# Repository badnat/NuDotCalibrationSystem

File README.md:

# NuDotCalibrationSystem

This project is for the NuDot Experiment https://jgruszko.web.unc.edu/experiments/. I am a student at UNC who will be graduating in May 2022. I am working with Dr. Gruszko to develop the code and electronics to control the calibration system for the NuDot experiment. The goal of this experiment is to detect neutrinoless double beta decay. Neutrinoless double beta decay is a very rare phenomenon. Because of this, it is difficult to distinguish signal from background during detection. NuDots goal is to reduce the background by detecting cherenkov radiation from single electron events produced by background events as opposed to the double electrons given off by double beta decay. 
 
The goal of my code and electronics is to move a point beta ray source to an exact height, inclination, and rotation. Knowing these allows NuDot to calibrate the precise timings given by the detectors. These timings are extremely important for event building, where we determine details about the event causing the signal such as the position and energy. 

## My Approach and Method
Having previously taken a class full dedicated to working with microcontrollers, my first thought for this project was to use a Raspberry Pi. I ruled out Arduinos because I needed a file system to save multiple files and wanted the flexibility of a microcontroller with an OS for testing purposes. The problem ultimately boils down to moving 3 stepper motors into position, verifying the accuracy of that position, and recording that position for and future movements of the stepper. 
 
I achieved these objectives by using python code to control the stepper motors and a c++ program to read the data from the stepper encoders, interpret the data, and store the position in a file. The python code will only move the stepper and the c++ code will only determine its position. This allows me to independently verify the positions of the steppers and compensate for any step skipping that might occur. This ensures that we always accurately know the positions of the steppers which is important for both calibration and mechanical reasons. Obviously we need to accurately know the position of the beta source to calibrate the system, but there are also a few mechanical hard stops that the steppers would be unable to push past (blocked by a lot of metal). I could have used a sensor to determine the position in space but decided to make my code very robust to avoid the issue all together. 

#### Code Structure
I decided on an object oriented approach for ease of use and abstraction. The [Calibrator](https://github.com/badnat/NuDotCalibrationSystem/blob/main/calibrator.py) object is primarily for abstraction and handling error handling/edge cases. It holds all of the [Stepper](https://github.com/badnat/NuDotCalibrationSystem/blob/main/stepper.py) objects which send the signals to the stepper motors to move them. The [Stepper](https://github.com/badnat/NuDotCalibrationSystem/blob/main/stepper.py) objects also use bash commands to start up the [encoder](https://github.com/badnat/NuDotCalibrationSystem/blob/main/encoder.cpp) code for that stepper motor. 

## Assembled Calibration System

## Challenges and Future Improvements
- Fully implementation of code and handling a few more edge cases (almost finished)
- Implement code for the Daq system to control the Rpi remotely using ssh keys
- Finalize Electronics using a custom PCB and CAT6 cable to send signals to the steppers and to the Pi from the encoders

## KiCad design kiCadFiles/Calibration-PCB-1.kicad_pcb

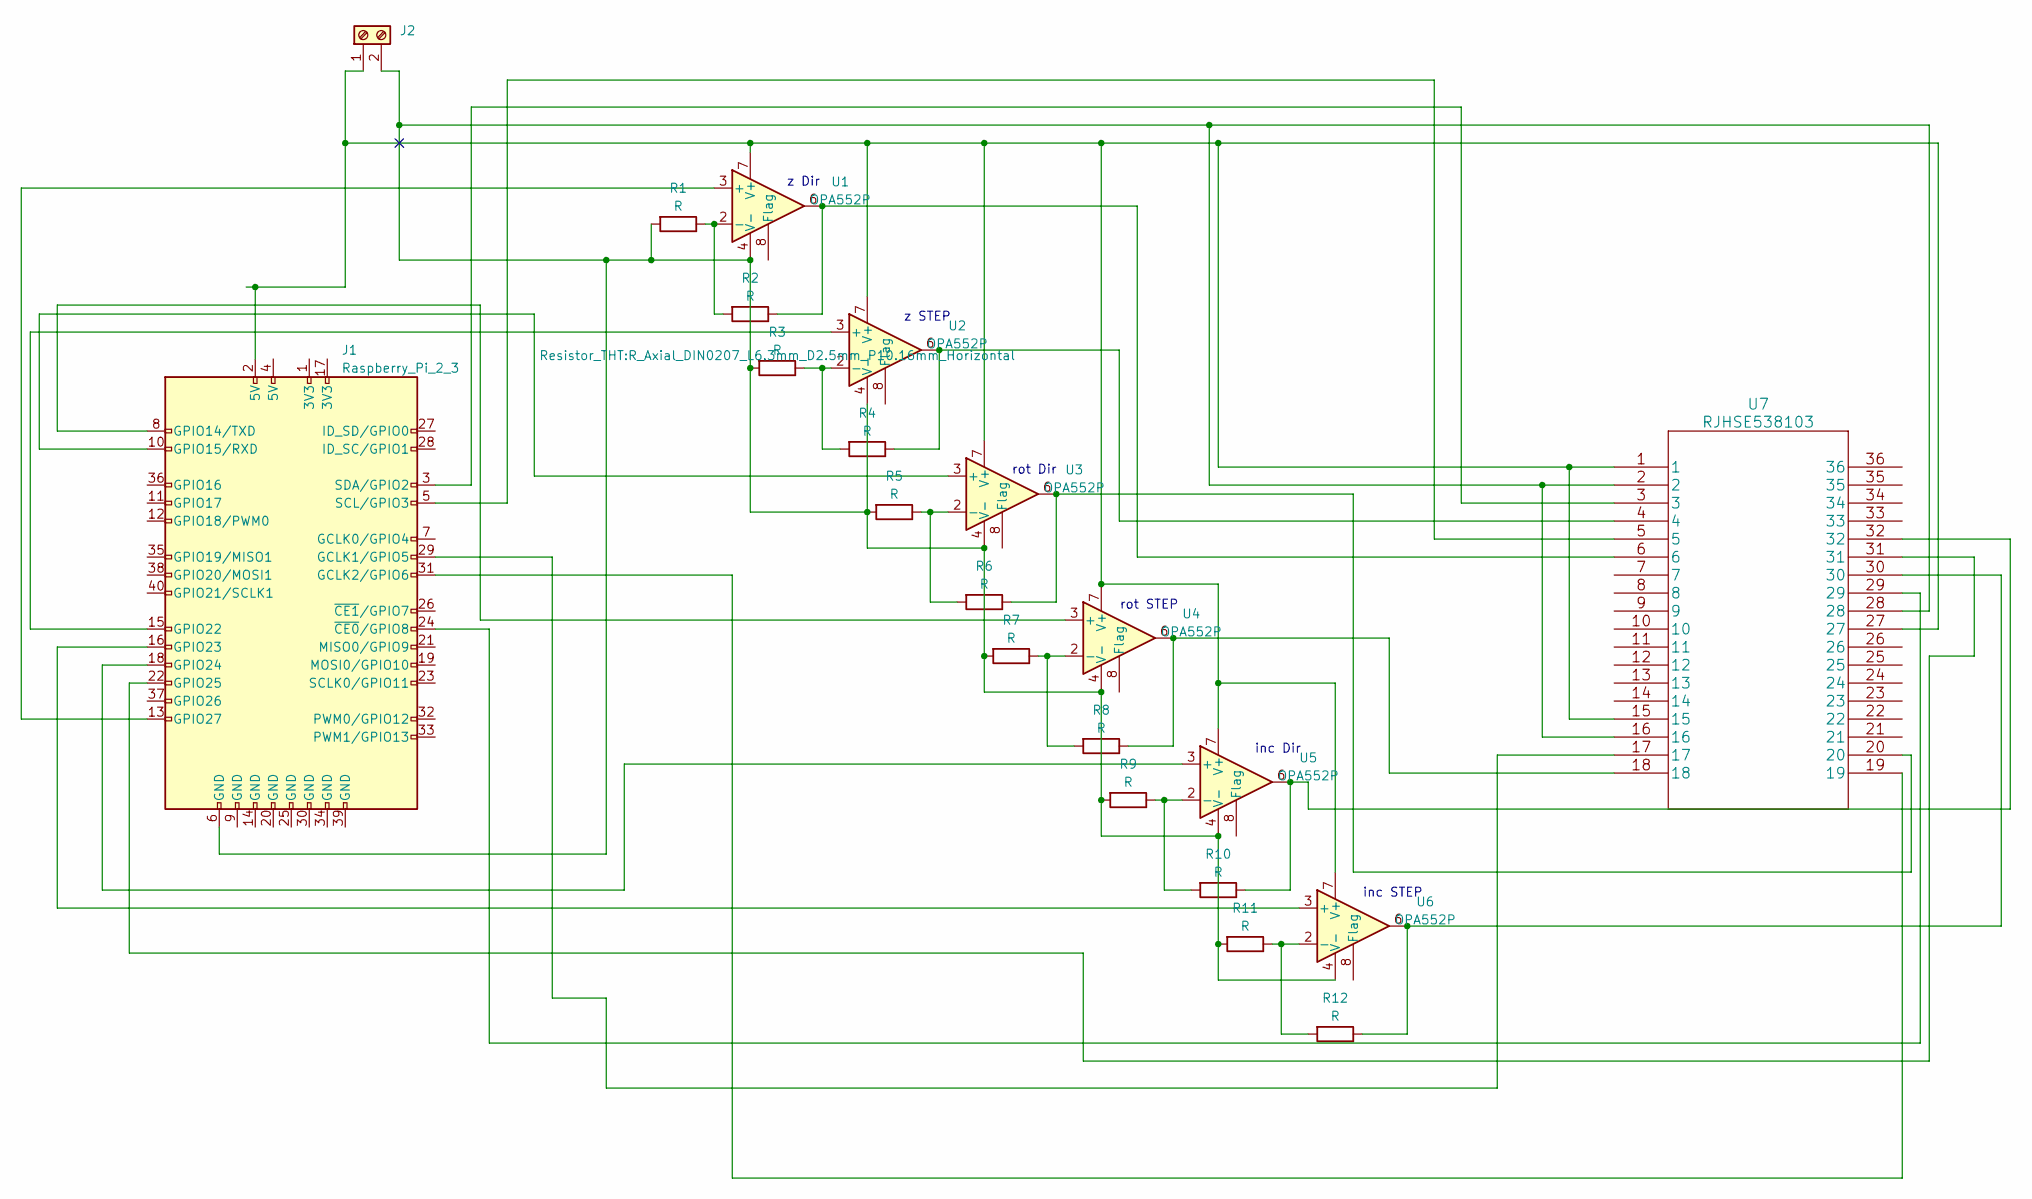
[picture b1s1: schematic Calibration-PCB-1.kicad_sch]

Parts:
J1: Raspberry_Pi_2_3; PinHeader_2x20_P2.54mm_Vertical
J2: (no value)
R1, R2, R3, R4, R5, R6, R7, R8, R9, R10, R11, R12: R; R_Axial_DIN0207_L6.3mm_D2.5mm_P10.16mm_Horizontal
U1, U2, U3, U4, U5, U6: OPA552P; DIP-8_W7.62mm
U7: RJHSE538103

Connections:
unnamed: J1.2 (5V), J2.1, U1.7 (V+), U2.7 (V+), U3.7 (V+), U4.7 (V+), U5.7 (V+), U6.7 (V+), U7.1, U7.15, U7.27
unnamed: J1.29 (GCLK1/GPIO5), U7.17
unnamed: J1.31 (GCLK2/GPIO6), U7.19
unnamed: J1.6 (GND), J2.2, R1.2, R3.2, R5.2, R7.2, R9.2, R11.2, U1.4 (V-), U2.4 (V-), U3.4 (V-), U4.4 (V-), U5.4 (V-), U6.4 (V-), U7.2, U7.16, U7.28
unnamed: J1.13 (GPIO27), U1.3 (+)
unnamed: J1.5 (SCL/GPIO3), U7.5
unnamed: J1.3 (SDA/GPIO2), U7.3
unnamed: R2.1, U1.6, U7.6
unnamed: R4.1, U2.6, U7.4
unnamed: R6.1, U3.6, U7.20
unnamed: R8.1, U4.6, U7.18
unnamed: R1.1, R2.2, U1.2 (-)
unnamed: J1.15 (GPIO22), U2.3 (+)
unnamed: R3.1, R4.2, U2.2 (-)
unnamed: J1.10 (GPIO15/RXD), U3.3 (+)
unnamed: R5.1, R6.2, U3.2 (-)
unnamed: J1.8 (GPIO14/TXD), U4.3 (+)
unnamed: R7.1, R8.2, U4.2 (-)
unnamed: J1.18 (GPIO24), U5.3 (+)
unnamed: R9.1, R10.2, U5.2 (-)
unnamed: J1.16 (GPIO23), U6.3 (+)
unnamed: R11.1, R12.2, U6.2 (-)
unnamed: J1.24 (~CE0/GPIO8), U7.29
unnamed: R12.1, U6.6, U7.30
unnamed: J1.22 (GPIO25), U7.31
unnamed: R10.1, U5.6, U7.32

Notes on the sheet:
rot STEP
rot Dir
z STEP
inc Dir
inc STEP
z Dir

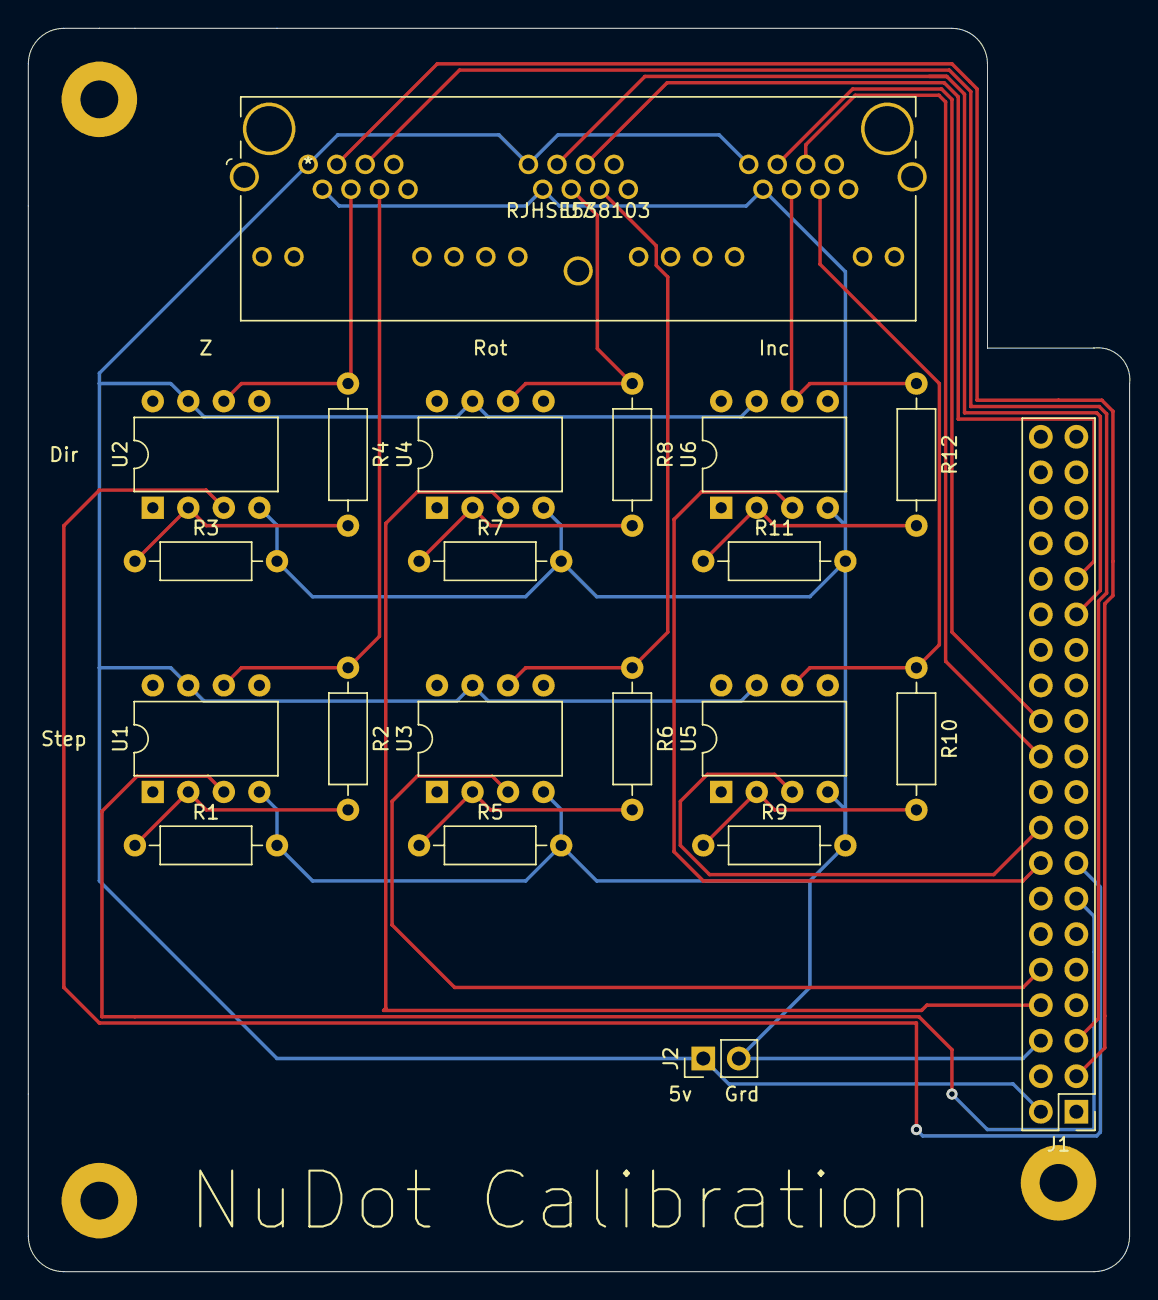
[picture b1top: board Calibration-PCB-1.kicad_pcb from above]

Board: 2 copper layers, 78.8 x 88.9 mm, 21 parts (0 on the bottom side), 26 nets.

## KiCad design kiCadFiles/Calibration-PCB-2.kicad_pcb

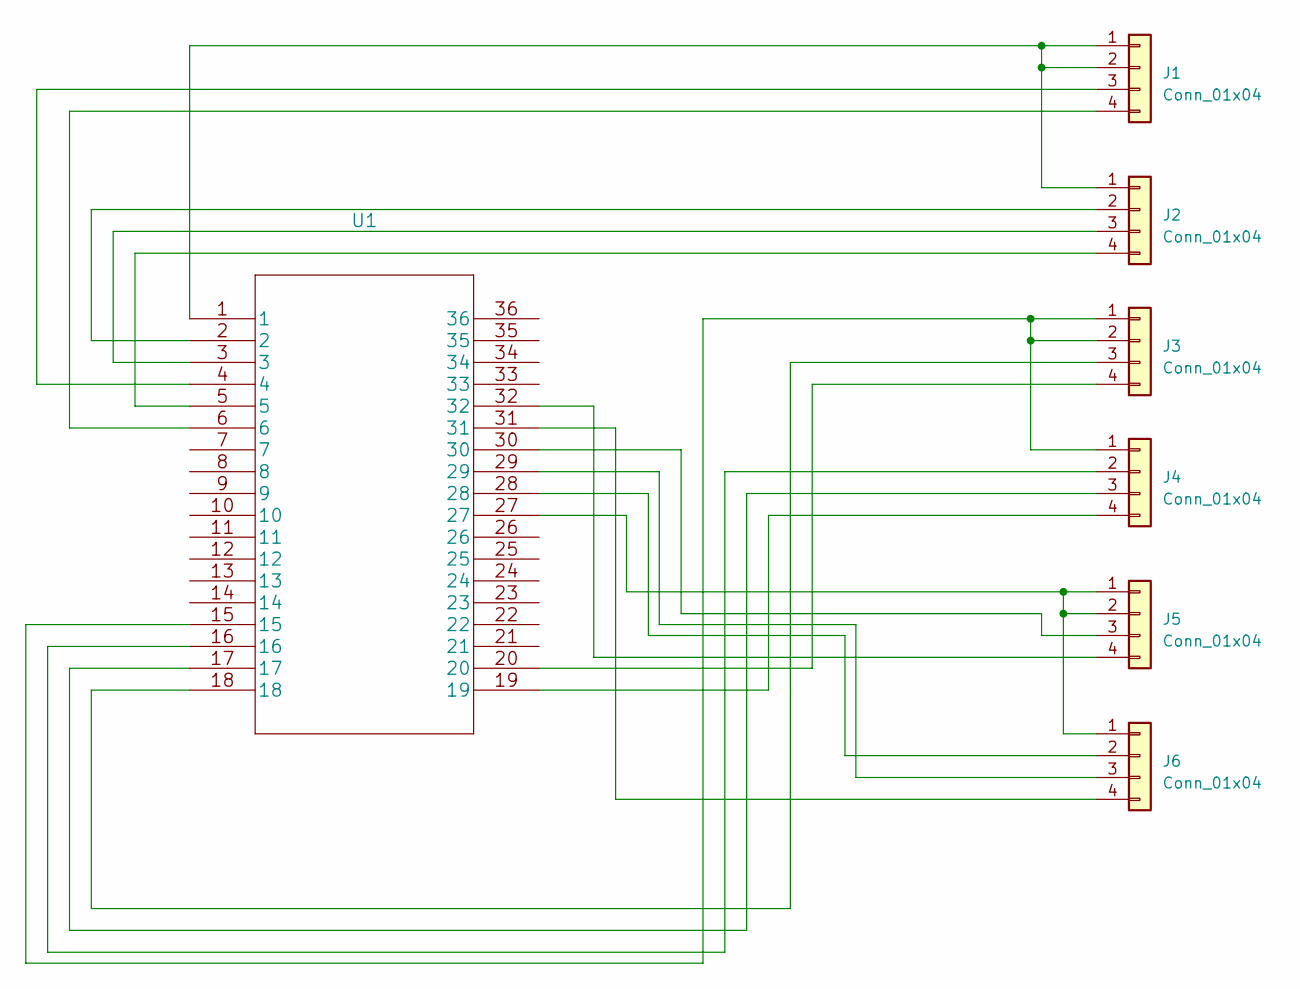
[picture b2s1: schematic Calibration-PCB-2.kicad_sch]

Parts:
J1, J2, J3, J4, J5, J6: Conn_01x04; PinSocket_1x04_P2.54mm_Vertical
U1: (no value)

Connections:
unnamed: J1.1, J1.2, J2.1, U1.1
unnamed: J1.3, U1.4
unnamed: J1.4, U1.6
unnamed: J2.2, U1.2
unnamed: J2.3, U1.3
unnamed: J2.4, U1.5
unnamed: J3.1, J3.2, J4.1, U1.15
unnamed: J3.3, U1.18
unnamed: J3.4, U1.20
unnamed: J4.2, U1.16
unnamed: J4.3, U1.17
unnamed: J4.4, U1.19
unnamed: J5.1, J5.2, J6.1, U1.27
unnamed: J5.3, U1.30
unnamed: J5.4, U1.32
unnamed: J6.2, U1.28
unnamed: J6.3, U1.29
unnamed: J6.4, U1.31

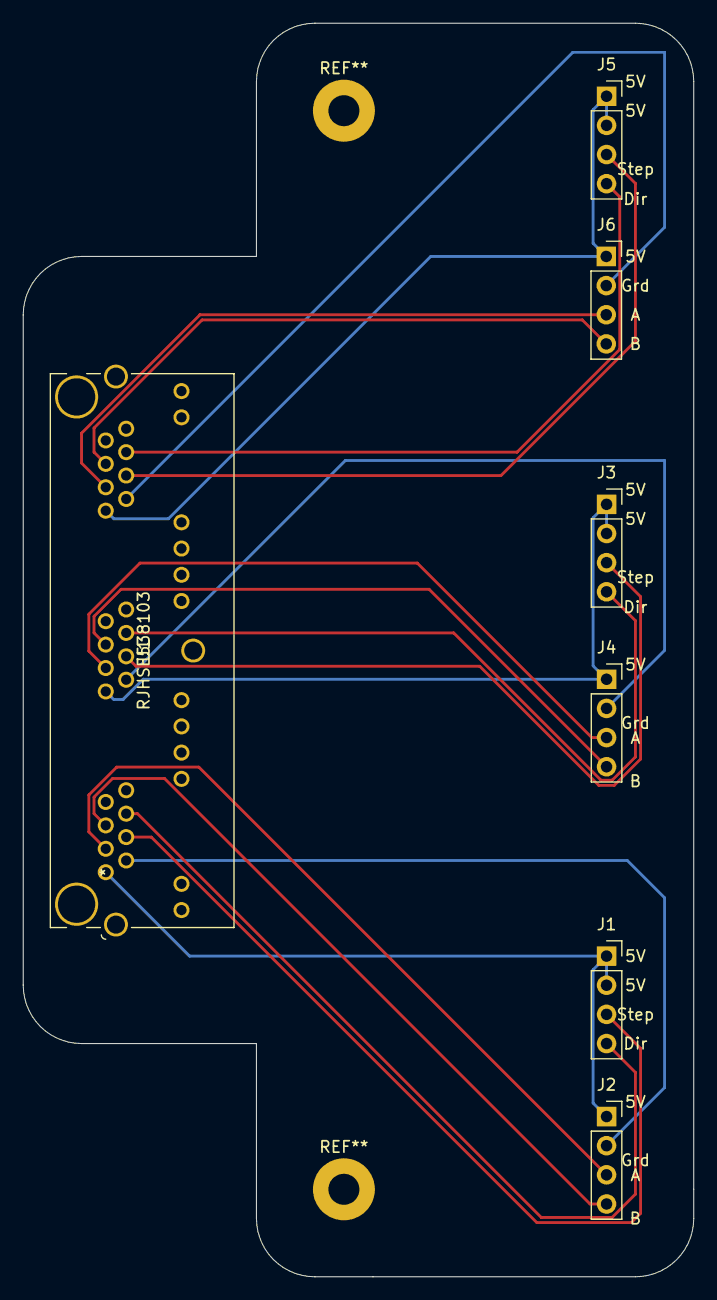
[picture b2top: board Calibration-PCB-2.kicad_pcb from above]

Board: 2 copper layers, 58.4 x 109.2 mm, 7 parts (0 on the bottom side), 18 nets.

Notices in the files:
parts and their libraries:
Copyright 2021 Accelerated Designs. All rights reserved.
